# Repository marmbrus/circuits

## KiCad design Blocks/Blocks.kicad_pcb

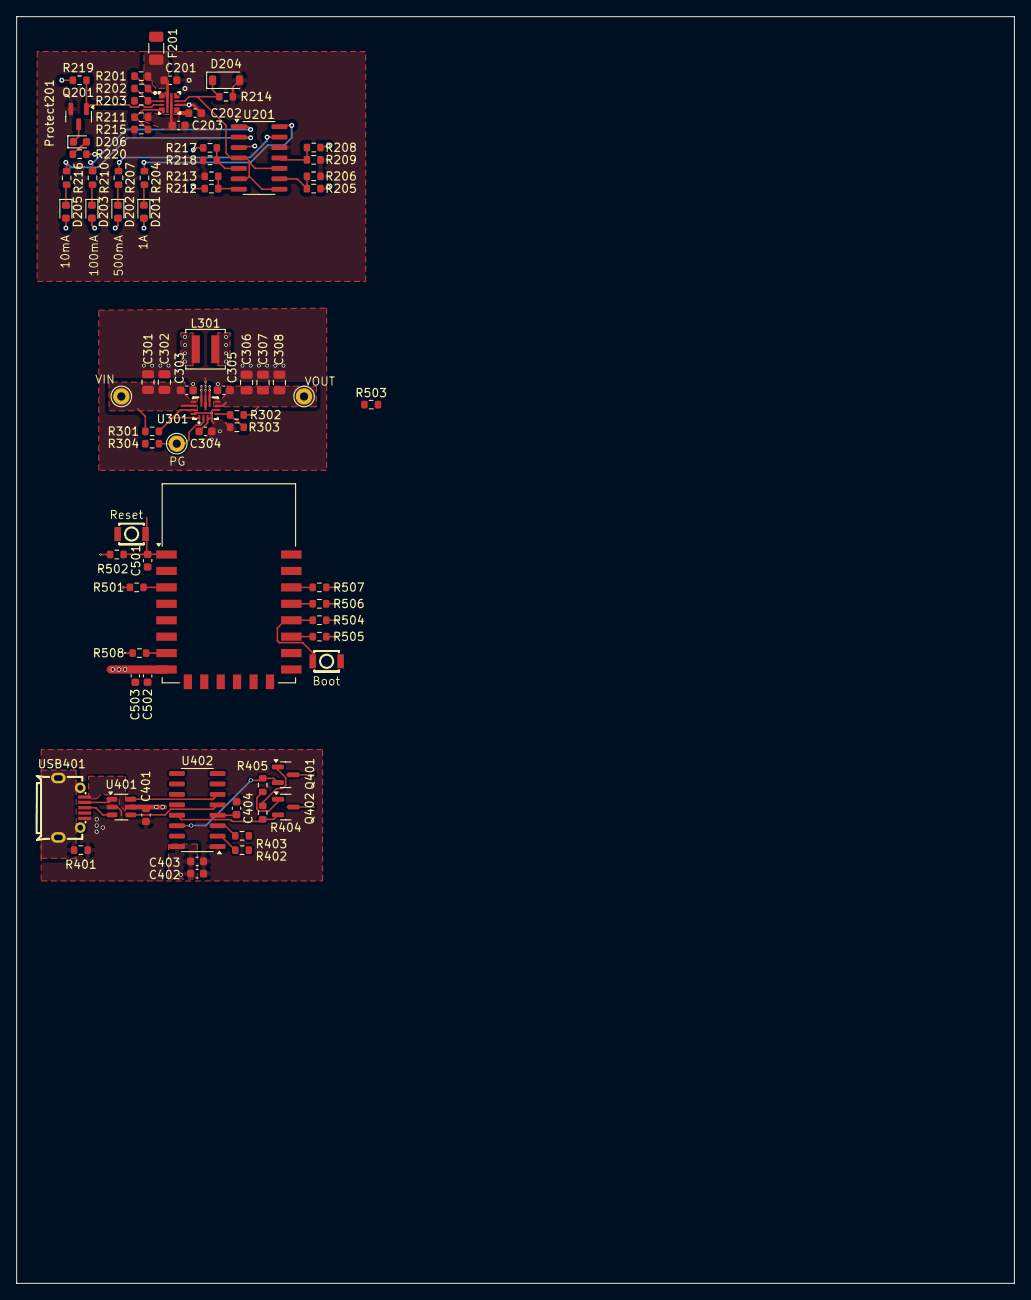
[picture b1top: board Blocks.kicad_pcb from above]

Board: 4 copper layers, 121.5 x 154.2 mm, 78 parts (0 on the bottom side), 54 nets.

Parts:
C201, C203: 1uf; C_0603_1608Metric
C202: 2.7nf; C_0603_1608Metric
C301, C302: 10uf; C_0805_2012Metric
C303, C305, C402, C502: 10uf; C_0603_1608Metric
C304, C401, C403, C404, C503: 100nf; C_0603_1608Metric
C306, C307, C308: 22uf; C_0805_2012Metric
C501: 470pf; C_0603_1608Metric
D201, D202, D203, D205, D206: LED; LED_0603_1608Metric
D204: 1.8V; D_SOD-123
F201: 2A; Fuse_1206_3216Metric
L301: 1uH; L_Coilcraft_XAL4020-XXX
Protect201: LM73100RPWR; VQFN-10_L2.0-W2.0-P0.45-TL
Q201: 2N7002; SOT-23
Q401, Q402: MMBT3904; SOT-23
R201, R211: 470k; R_0603_1608Metric
R202: 196k; R_0603_1608Metric
R203: 54.9k; R_0603_1608Metric
R204, R207, R210, R216, R220: 150; R_0603_1608Metric
R205: 5.6k; R_0603_1608Metric
R206, R209, R213, R218: 1k; R_0603_1608Metric
R208, R404, R405: 12k; R_0603_1608Metric
R212: 68k; R_0603_1608Metric
R214: 4120; R_0603_1608Metric
R215: 249k; R_0603_1608Metric
R217: 680k; R_0603_1608Metric
R219, R301, R304, R501, R502, R503, R504, R505: 10k; R_0603_1608Metric
R302: 332k; R_0603_1608Metric
R303: 51k; R_0603_1608Metric
R401: 0; R_0603_1608Metric
R402, R403: 480; R_0603_1608Metric
R506, R507, R508: 4.7k; R_0603_1608Metric
SW501, SW502: B3U-1000P; KEY-SMD_B3U-1000PM
TP301, TP302, TP303: TestPoint; Pin_D1.0mm_L10.0mm
U201: LM339; SOIC-14_3.9x8.7mm_P1.27mm
U301: TPS63070RNMR; VQFN-HR-15_L3.0-W2.5-P0.50-BL_TPS63070RNMR
U401: USBLC6-2SC6; SOT-23-6
U402: CH340C; SOIC-16_3.9x9.9mm_P1.27mm
U501: ESP-12F; ESP-12E
USB401: MICROXNJ; MICRO-USB-SMD_MICROXNJ

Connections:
+5V: D201.2 (A), D202.2 (A), D203.2 (A), D205.2 (A), R205.1, R208.1, R212.1, R217.1, R219.1, R220.2, U201.3 (V+)
/BB6V/PG: R304.2, TP302.1, U301.2 (PG)
/BB6V/VIN: C301.1, C302.1, C303.1, R301.1, TP301.1, U301.12 (Vin), U301.13 (Vin)
/BB6V/VOUT: C305.1, C306.1, C307.1, C308.1, R302.1, TP303.1, U301.7 (Vout), U301.8 (Vout)
/ESP12F/3V3: C502.1, C503.1, R501.1, R502.1, R504.1, R505.1, R506.1, R507.1, R508.1, U501.8 (VCC)
/ESP12F/BOOT: R504.2, SW502.1, U501.18 (GPIO0)
/ESP12F/ONEW: R508.2, U501.7 (GPIO13)
/ESP12F/RST: C501.2, R502.2, SW501.2, U501.1 (~RST)
/ESP12F/SCL: R507.2, U501.20 (GPIO5)
/ESP12F/SDA: R506.2, U501.19 (GPIO4)
/PP3V16V/Fused: C201.2, F201.2, Protect201.5 (IN), R201.2
/PP3V16V/IMON: D204.1 (C), Protect201.9 (IMON), R214.2, U201.4 (-), U201.6 (-), U201.8 (-), U201.10 (-)
/PP3V16V/PG: Protect201.3 (PG), Q201.1 (G), R219.2
/PP3V16V/VOUT: C203.2, Protect201.6 (OUT), R211.2
/usb_serial/VUSB: C401.1, C402.1, C403.1, U401.5 (VBUS), U402.16 (VCC), USB401.1 (VBUS)
GND: C201.1, C202.2, C203.1, C301.2, C302.2, C303.2, C304.2, C305.2, C306.2, C307.2, C308.2, C401.2, C402.2, C403.2, C404.1, C501.1, C502.2, C503.2, D204.2 (A), Protect201.8 (GND), Q201.2 (S), R203.1, R206.2, R209.2, R213.2, R214.1, R215.1, R218.2, R303.2, R401.2, R503.2, SW501.1, SW502.2, U201.12 (V-), U301.4 (GND), U301.6 (FB2), U301.10 (PGND), U301.15 (Vsel), U401.2 (GND), U402.1 (GND), U501.15 (GND), USB401.5 (GND)
unnamed: D201.1 (K), R204.2
unnamed: D202.1 (K), R207.2
unnamed: D203.1 (K), R210.2
unnamed: D205.1 (K), R216.2
unnamed: D206.2 (A), R220.1
unnamed: D206.1 (K), Q201.3 (D)
unnamed: C202.1, Protect201.7 (DVDT)
unnamed: Protect201.1 (EN/UVLO), R201.1, R202.2
unnamed: Protect201.2 (OVLO), R202.1, R203.2
unnamed: Protect201.4 (PGTH), R211.1, R215.2
unnamed: Q401.1 (B), R404.1
unnamed: Q401.2 (E), R405.2, U402.14 (~RTS)
unnamed: Q402.1 (B), R405.1
unnamed: Q402.2 (E), R404.2, U402.13 (~DTR)
unnamed: R204.1, U201.14
unnamed: R207.1, U201.13
unnamed: R210.1, U201.1
unnamed: R216.1, U201.2
unnamed: R217.2, R218.1, U201.5 (+)
unnamed: R212.2, R213.1, U201.7 (+)
unnamed: R208.2, R209.1, U201.11 (+)
unnamed: R205.2, R206.1, U201.9 (+)
unnamed: R301.2, U301.1 (PS/SYNC), U301.14 (EN)
unnamed: R302.2, R303.1, U301.5 (FB)
unnamed: L301.1, U301.11 (L1)
unnamed: L301.2, U301.9 (L2)
unnamed: C304.1, U301.3 (Vaux)
unnamed: R403.2, U402.3 (RXD)
unnamed: R402.1, U402.2 (TXD)
unnamed: U401.4 (I/O2), U402.5 (UD+)
unnamed: U401.6 (I/O1), U402.6 (UD-)
unnamed: C404.2, U402.4 (V3)
unnamed: R501.2, U501.3 (EN)
unnamed: R505.2, U501.17 (GPIO2)
unnamed: R503.1, U501.16 (GPIO15)
unnamed: U401.3 (I/O2), USB401.3 (D+)
unnamed: U401.1 (I/O1), USB401.2 (D-)
unnamed: R401.1, USB401.6 (SH1), USB401.7 (SH2), USB401.8 (SH3), USB401.9 (SH4)

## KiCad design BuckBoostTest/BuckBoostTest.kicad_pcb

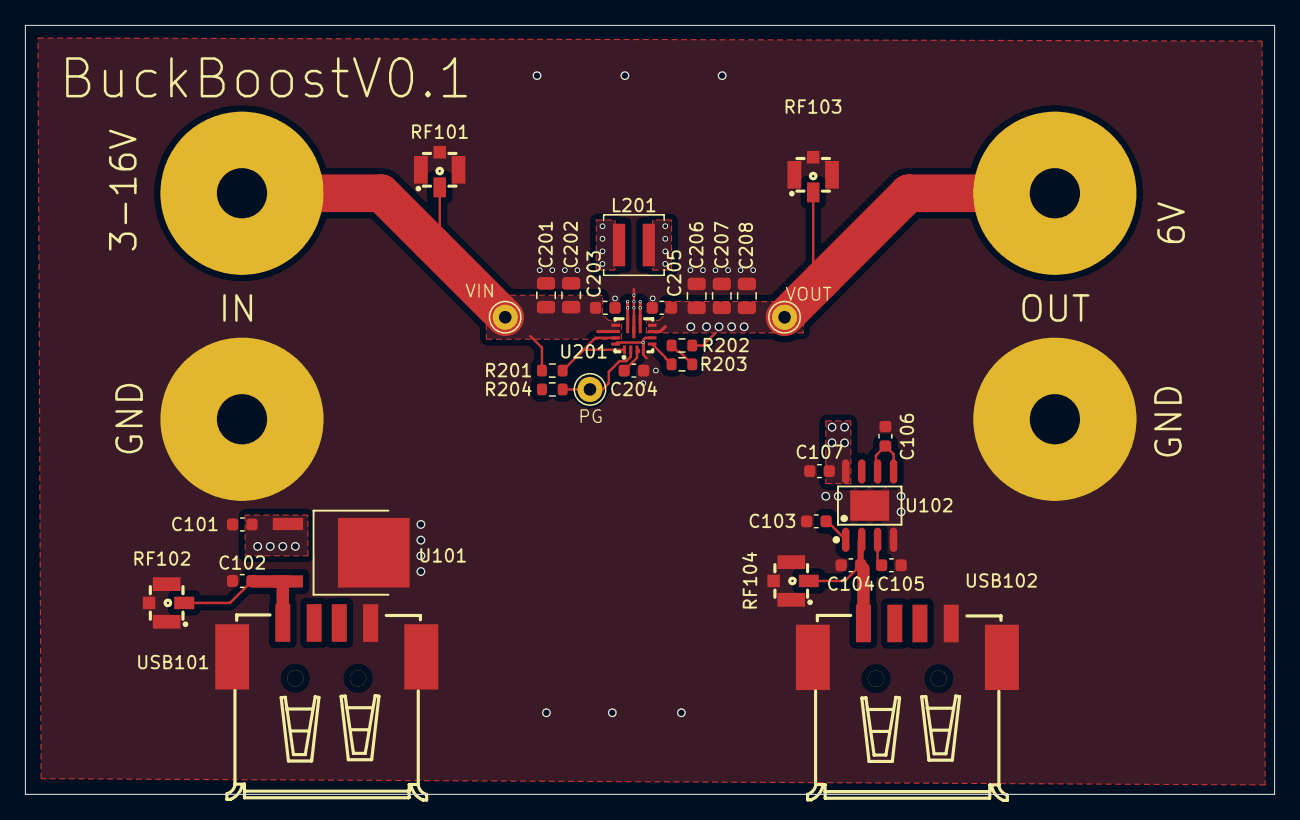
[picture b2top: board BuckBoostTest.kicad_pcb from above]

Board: 4 copper layers, 99.5 x 61.2 mm, 36 parts (0 on the bottom side), 15 nets.

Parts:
BP101, BP102, BP103, BP104: BananaPlug
C101, C102, C103, C104, C107, C203, C205: 10uf; C_0603_1608Metric
C105, C106: 1uf; C_0603_1608Metric
C201, C202: 10uf; C_0805_2012Metric
C204: 100nf; C_0603_1608Metric
C206, C207, C208: 22uf; C_0805_2012Metric
L201: 1uH; L_Coilcraft_XAL4020-XXX
R201, R204: 10k; R_0603_1608Metric
R202: 332k; R_0603_1608Metric
R203: 51k; R_0603_1608Metric
RF101, RF102, RF103, RF104: 73412-0110; ANT-SMD_73412-0110
TP201, TP202, TP203: TestPoint; Pin_D1.0mm_L10.0mm
U101: MC7805CDTRKG; TO-252-2_L6.6-W6.1-P4.58-LS9.9-TL
U102: ADM7150ARDZ-5.0; SOIC-8_L4.9-W3.9-P1.27-LS6.0-BL-EP
U201: TPS63070RNMR; VQFN-HR-15_L3.0-W2.5-P0.50-BL_TPS63070RNMR
USB101, USB102: AF180QT1.0; USB-A-SMD_AF180QT1.0

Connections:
/BB6V/PG: R204.2, TP202.1, U201.2 (PG)
/BB6V/VIN: BP101.1 (IN), C201.1, C202.1, C203.1, R201.1, RF101.2 (SIG), TP201.1, U201.12 (Vin), U201.13 (Vin)
/BB6V/VOUT: BP103.1 (IN), C101.2, C107.1, C205.1, C206.1, C207.1, C208.1, R202.1, RF103.2 (SIG), TP203.1, U101.1 (Input), U102.7 (EN), U102.8 (VIN), U201.7 (Vout), U201.8 (Vout)
GND: BP102.1 (IN), BP104.1 (IN), C101.1, C102.1, C103.2, C104.2, C105.2, C106.2, C107.2, C201.2, C202.2, C203.2, C204.2, C205.2, C206.2, C207.2, C208.2, RF101.1 (GND), RF101.3 (GND), RF101.4 (GND), RF102.1 (GND), RF102.3 (GND), RF102.4 (GND), RF103.1 (GND), RF103.3 (GND), RF103.4 (GND), RF104.1 (GND), RF104.3 (GND), RF104.4 (GND), U101.2 (Ground), U102.4 (GND), U102.9 (EP), U201.4 (GND), U201.6 (FB2), U201.10 (PGND), U201.15 (Vsel), USB101.4 (GND), USB101.5 (SH1), USB101.6 (SH2), USB102.4 (GND), USB102.5 (SH1), USB102.6 (SH2)
unnamed: R202.2, R203.1
unnamed: C102.2, RF102.2 (SIG), U101.3 (Output), USB101.1 (VCC)
unnamed: C104.1, RF104.2 (SIG), U102.2 (VOUT), USB102.1 (VCC)
unnamed: C105.1, U102.3 (BYP)
unnamed: C106.1, U102.5 (REF_SENSE), U102.6 (REF)
unnamed: C103.1, U102.1 (VREG)
unnamed: R201.2, U201.1 (PS/SYNC), U201.14 (EN)
unnamed: R203.2, U201.5 (FB)
unnamed: L201.1, U201.11 (L1)
unnamed: L201.2, U201.9 (L2)
unnamed: C204.1, U201.3 (Vaux)

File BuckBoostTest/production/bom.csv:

Designator,Footprint,Quantity,Value,LCSC Part #
"C101, C103, C104, C106, C107, C203, C205",0603,7,10uf,
"C102, C105",0603,2,1uf,
"C201, C202",0805,2,10uf,
C204,0603,1,100nf,
"C206, C207, C208",0805,3,22uf,
L201,L_Coilcraft_XAL4020-XXX,1,1uH,C4555951
"R201, R204",0603,2,10k,
R202,0603,1,332k,
R203,0603,1,51k,
"RF101, RF102, RF103, RF104",ANT-SMD_73412-0110,4,73412-0110,C434806
U101,TO-252-2_L6.6-W6.1-P4.58-LS9.9-TL,1,MC7805CDTRKG,C54285
U102,SOIC-8_L4.9-W3.9-P1.27-LS6.0-BL-EP,1,ADM7150ARDZ-5.0,C208034
U201,VQFN-HR-15_L3.0-W2.5-P0.50-BL_TPS63070RNMR,1,TPS63070RNMR,C109322
"USB101, USB102",USB-A-SMD_AF180QT1.0,2,AF180QT1.0,C404963

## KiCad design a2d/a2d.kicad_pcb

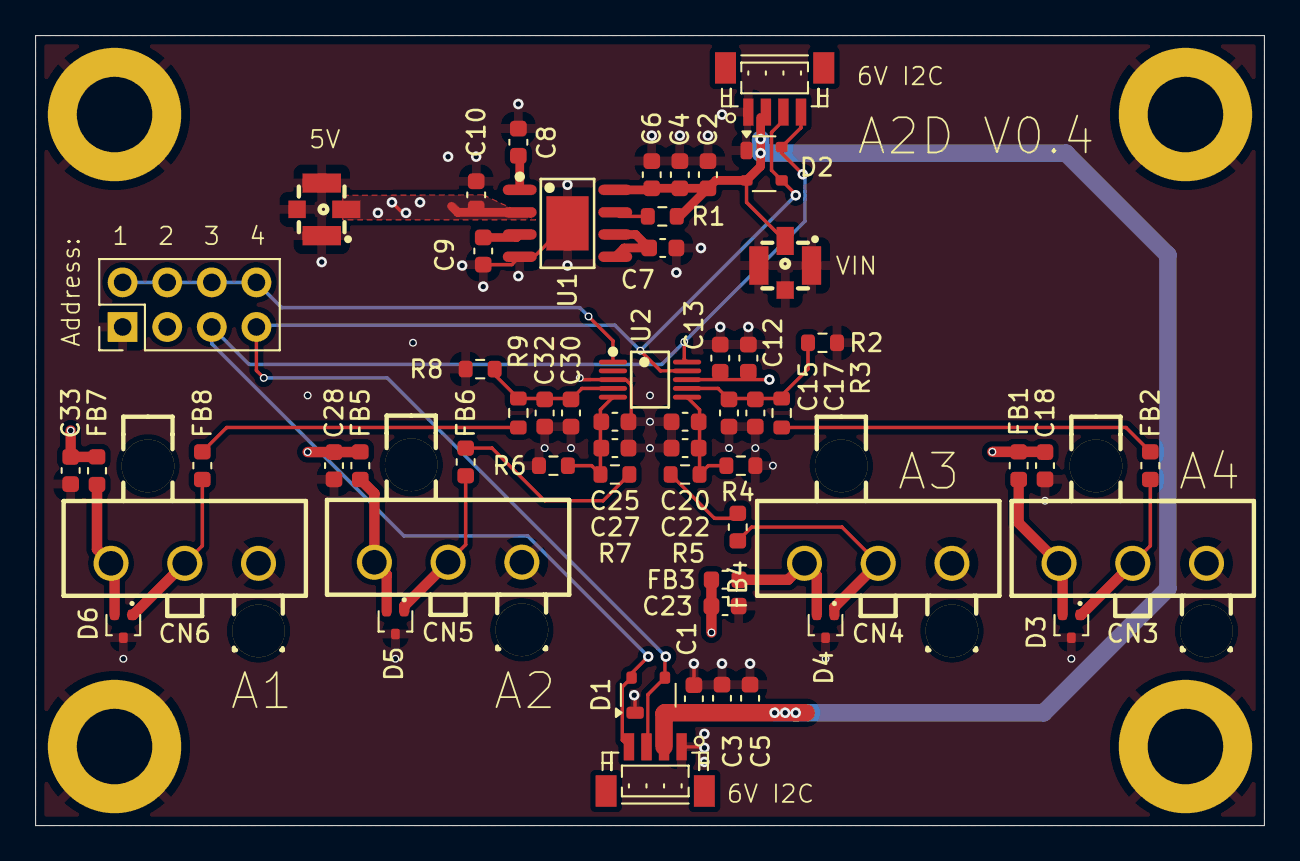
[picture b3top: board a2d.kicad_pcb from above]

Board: 4 copper layers, 70.0 x 45.0 mm, 62 parts (0 on the bottom side), 26 nets.

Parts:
C1, C2, C13: 100nf; C_0603_1608Metric
C3, C4, C7, C9, C12: 1uf; C_0603_1608Metric
C5, C6, C8, C10: 10uf; C_0603_1608Metric
C15, C18, C20, C23, C25, C28, C30, C33: 100nF; C_0603_1608Metric
C17, C22, C27, C32: 3.3uF; C_0603_1608Metric
CN1, CN2: BM04B-SRSS-TB(LF)(SN); CONN-SMD_BM04B-SRSS-TB
CN3, CN4, CN5, CN6: 39302030; CONN-TH_3P-P4.20_39302030
D1, D2: SP0503BAHT; SOT-143
D3, D4, D5, D6: RCLAMP0502B; SOT-416
FB1, FB2, FB3, FB4, FB5, FB6, FB7, FB8: FerriteBead; L_0603_1608Metric
H1, H2, H3, H4: MountingHole_Pad; MountingHole_4.3mm_M4_ISO7380_Pad
J1: Conn_02x04_Odd_Even; PinHeader_2x04_P2.54mm_Vertical
R1, R3, R5, R7, R9: 10k; R_0603_1608Metric
R2, R4, R6, R8: 5.1M; R_0603_1608Metric
RF1, RF2: 73412-0110; ANT-SMD_73412-0110
U1: ADM7150ARDZ-5.0; SOIC-8_L4.9-W3.9-P1.27-LS6.0-BL-EP
U2: ADS1115IDGSR; MSOP-10_L3.0-W3.0-P0.50-LS5.0-BL

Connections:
+5V: C10.1, C12.1, C13.1, C18.1, C23.1, C28.1, C33.1, FB1.2, FB3.2, FB5.2, FB7.2, J1.3, RF2.2 (SIG), U1.2 (VOUT), U2.8 (VDD)
/6V: C1.1, C2.1, C3.1, C4.1, C5.1, C6.1, CN1.2, CN2.2, D1.2 (K), D2.2 (K), R1.1, RF1.2 (SIG), U1.8 (VIN)
/A1: C30.2, C32.2, R8.2, R9.1, U2.4 (AIN0)
/A2: C25.2, C27.2, R6.2, R7.1, U2.5 (AIN1)
/A3: C20.2, C22.2, R4.2, R5.1, U2.6 (AIN2)
/A4: C15.2, C17.2, R2.2, R3.1, U2.7 (AIN3)
/SCL: CN1.4, CN2.4, D1.4 (K), D2.4 (K), J1.5, U2.10 (SCL)
/SDA: CN1.3, CN2.3, D1.3 (K), D2.3 (K), J1.7, U2.9 (SDA)
GND: C1.2, C2.2, C3.2, C4.2, C5.2, C6.2, C7.1, C8.2, C9.1, C10.2, C12.2, C13.2, C15.1, C17.1, C18.2, C20.1, C22.1, C23.2, C25.1, C27.1, C28.2, C30.1, C32.1, C33.2, CN1.1, CN2.1, CN3.3, CN4.3, CN5.3, CN6.3, D1.1 (A), D2.1 (A), D3.3 (A), D4.3 (A), D5.3 (A), D6.3 (A), H1.1, H2.1, H3.1, H4.1, J1.1, R2.1, R4.1, R6.1, R8.1, RF1.1 (GND), RF1.3 (GND), RF1.4 (GND), RF2.1 (GND), RF2.3 (GND), RF2.4 (GND), U1.4 (GND), U1.9 (EP), U2.3 (GND)
unnamed: CN3.2, D3.1 (K1), FB2.1
unnamed: CN3.1, D3.2 (K2), FB1.1
unnamed: CN4.2, D4.1 (K1), FB4.1
unnamed: CN4.1, D4.2 (K2), FB3.1
unnamed: CN5.2, D5.1 (K1), FB6.1
unnamed: CN5.1, D5.2 (K2), FB5.1
unnamed: CN6.2, D6.1 (K1), FB8.1
unnamed: CN6.1, D6.2 (K2), FB7.1
unnamed: FB2.2, R3.2
unnamed: FB4.2, R5.2
unnamed: FB6.2, R7.2
unnamed: FB8.2, R9.2
unnamed: J1.2, J1.4, J1.6, J1.8, U2.1 (ADDR)
unnamed: C9.2, U1.3 (BYP)
unnamed: R1.2, U1.7 (EN)
unnamed: C7.2, U1.5 (REF_SENSE), U1.6 (REF)
unnamed: C8.1, U1.1 (VREG)

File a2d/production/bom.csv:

Designator,Footprint,Quantity,Value,LCSC Part #
"C1, C13, C15, C18, C2, C20, C23, C25, C28, C30, C33",0603,11,100nf,
"C10, C5, C6, C8",0603,4,10uf,
"C12, C3, C4, C7, C9",0603,5,1uf,
"C17, C22, C27, C32",0603,4,3.3uF,
"CN1, CN2",CONN-SMD_BM04B-SRSS-TB,2,BM04B-SRSS-TB(LF)(SN),C160390
"CN3, CN4, CN5, CN6",CONN-TH_3P-P4.20_39302030,4,39302030,C589033
"D1, D2",SOT-143,2,SP0503BAHT,
"D3, D4, D5, D6",SOT-416,4,RCLAMP0502B,
"FB1, FB2, FB3, FB4, FB5, FB6, FB7, FB8",0603,8,FerriteBead,C85824
J1,PinHeader_2x04_P2.54mm_Vertical,1,Conn_02x04_Odd_Even,C5383105
"R1, R3, R5, R7, R9",0603,5,10k,
"R2, R4, R6, R8",0603,4,5.1M,
U1,SOIC-8_L4.9-W3.9-P1.27-LS6.0-BL-EP,1,ADM7150ARDZ-5.0,C208034
U2,MSOP-10_L3.0-W3.0-P0.50-LS5.0-BL,1,ADS1115IDGSR,C37593

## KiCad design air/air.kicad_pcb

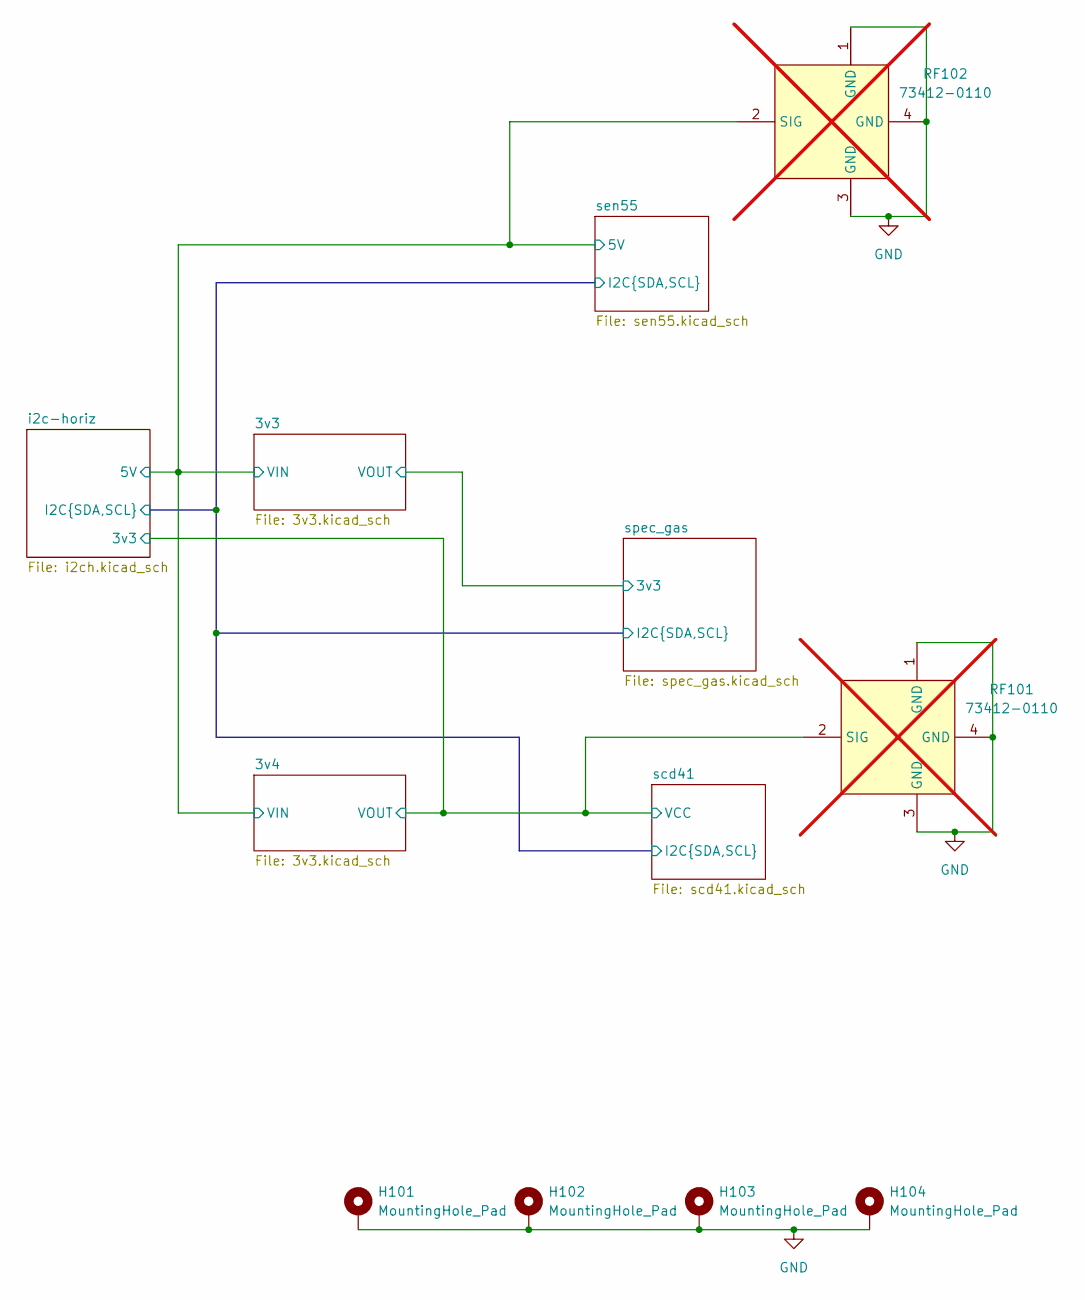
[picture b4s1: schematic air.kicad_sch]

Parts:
H101, H102, H103, H104: MountingHole_Pad; MountingHole_3.2mm_M3_Pad_Via
RF101, RF102: 73412-0110; ANT-SMD_73412-0110; LCSC Part C434806; not fitted

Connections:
/3v3/VIN: RF102.2 (SIG); also elsewhere on the board
/3v4/VOUT: RF101.2 (SIG); also elsewhere on the board
GND: H101.1, H102.1, H103.1, H104.1, RF101.1 (GND), RF101.3 (GND), RF101.4 (GND), RF102.1 (GND), RF102.3 (GND), RF102.4 (GND); also elsewhere on the board

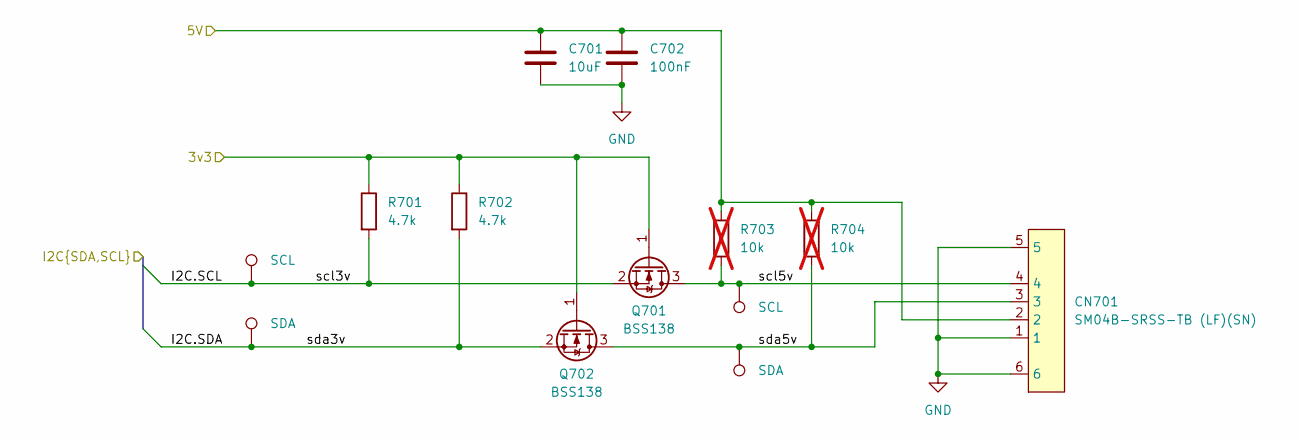
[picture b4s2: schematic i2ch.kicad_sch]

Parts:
C701: 10uF; C_0603_1608Metric
C702: 100nF; C_0603_1608Metric
CN701: SM04B-SRSS-TB (LF)(SN); CONN-SMD_4P-P1.00_SM04B-SRSS-TB-LF-SN; LCSC Part C160404
Q701, Q702: BSS138; SOT-23
R701, R702: 4.7k; R_0603_1608Metric
R703, R704: 10k; R_0603_1608Metric; not fitted
TP701, TP702, TP703, TP704: LabeledTestPoint

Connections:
/3v3/VIN: C701.1, C702.1, CN701.2, R703.1, R704.1; also elsewhere on the board
/3v4/VOUT: Q701.1 (G), Q702.1 (G), R701.1, R702.1; also elsewhere on the board
/i2c-horiz/I2C.SCL: Q701.2 (S), R701.2, TP701.1; also elsewhere on the board
/i2c-horiz/I2C.SDA: Q702.2 (S), R702.2, TP703.1; also elsewhere on the board
/i2c-horiz/scl5v: CN701.4, Q701.3 (D), R703.2, TP702.1
/i2c-horiz/sda5v: CN701.3, Q702.3 (D), R704.2, TP704.1
GND: C701.2, C702.2, CN701.1, CN701.5, CN701.6; also elsewhere on the board

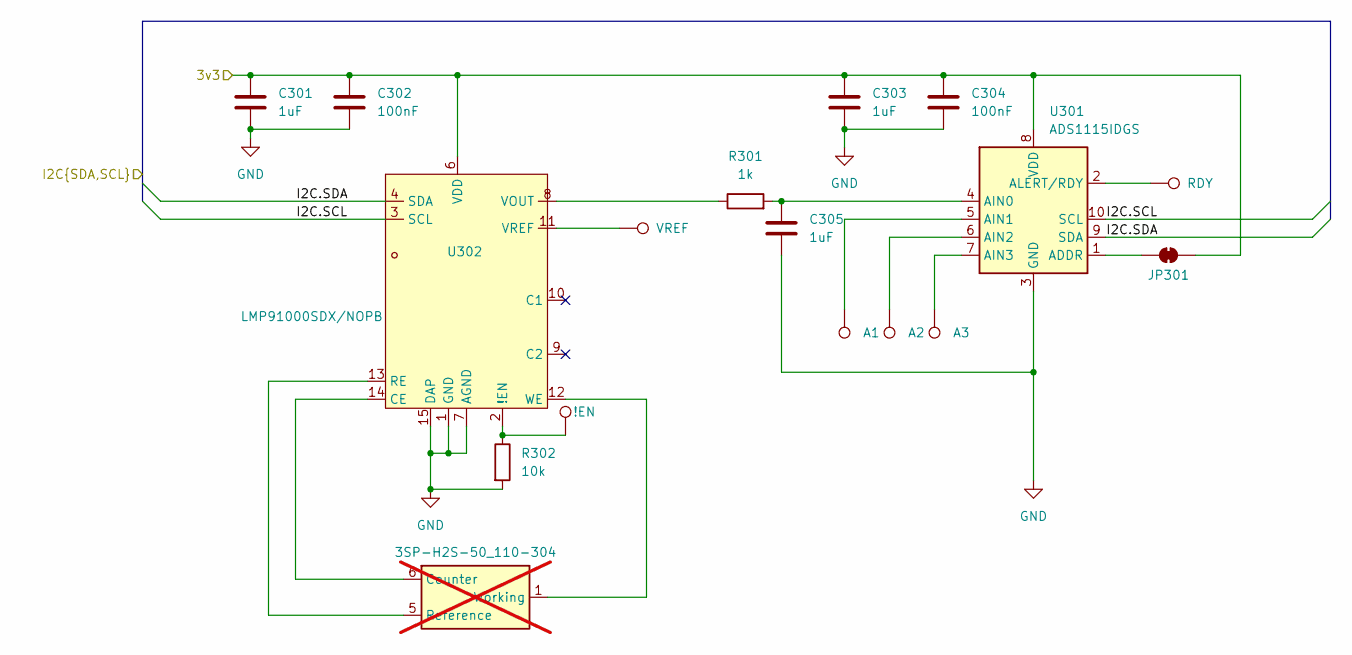
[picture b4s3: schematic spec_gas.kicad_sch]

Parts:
C301, C303, C305: 1uF; C_0603_1608Metric
C302, C304: 100nF; C_0603_1608Metric
JP301: SolderJumper_2_Bridged; SolderJumper-2_P1.3mm_Bridged2Bar_RoundedPad1.0x1.5mm
R301: 1k; R_0603_1608Metric
R302: 10k; R_0603_1608Metric
TP301, TP302, TP303, TP304, TP305, TP306: LabeledTestPoint
U301: ADS1115IDGS; TSSOP-10_3x3mm_P0.5mm
U302: LMP91000SDX/NOPB; WSON-14_L4.0-W4.0-P0.50-BL-EP-1; LCSC Part C2651584
U303: 3SP-H2S-50_110-304; SPEC_110-xxx_SMD-10Pin_20x20mm_P4.0mm; not fitted

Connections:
/3v3/VOUT: C301.1, C302.1, C303.1, C304.1, JP301.1 (A), U301.8 (VDD), U302.6 (VDD); also elsewhere on the board
/i2c-horiz/I2C.SCL: U301.10 (SCL), U302.3 (SCL); also elsewhere on the board
/i2c-horiz/I2C.SDA: U301.9 (SDA), U302.4 (SDA); also elsewhere on the board
GND: C301.2, C302.2, C303.2, C304.2, C305.2, R302.2, U301.3 (GND), U302.1 (GND), U302.7 (AGND), U302.15 (DAP); also elsewhere on the board
unnamed: JP301.2 (B), U301.1 (ADDR)
unnamed: C305.1, R301.2, U301.4 (AIN0)
unnamed: TP303.1, U301.5 (AIN1)
unnamed: TP304.1, U301.6 (AIN2)
unnamed: TP305.1, U301.7 (AIN3)
unnamed: TP301.1, U301.2 (ALERT/RDY)
unnamed: R302.1, TP306.1, U302.2 (!EN)
unnamed: U302.14 (CE), U303.6 (Counter)
unnamed: U302.13 (RE), U303.5 (Reference)
unnamed: R301.1, U302.8 (VOUT)
unnamed: TP302.1, U302.11 (VREF)
unnamed: U302.12 (WE), U303.1 (Working), U303.10 (Working)

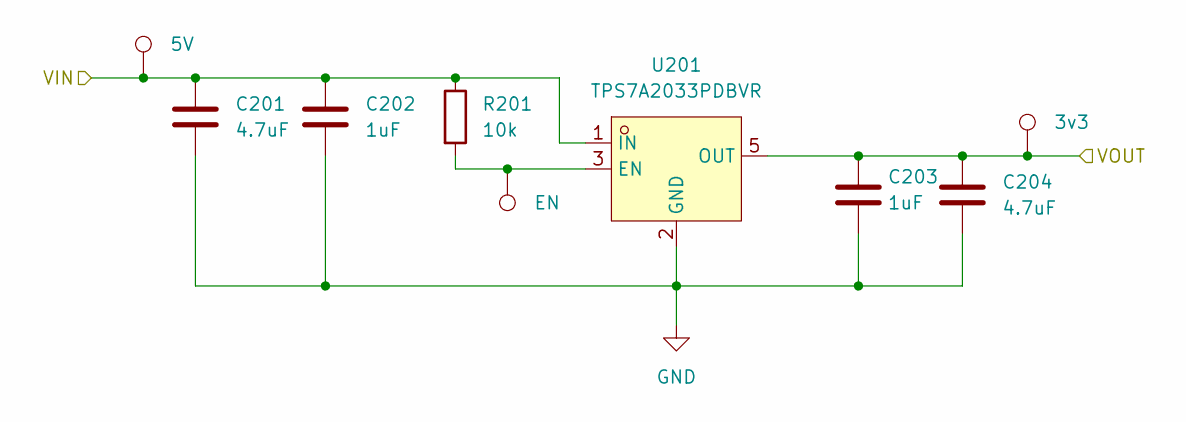
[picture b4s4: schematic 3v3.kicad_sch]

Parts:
C201, C204: 4.7uF; C_0603_1608Metric
C202, C203: 1uF; C_0603_1608Metric
R201: 10k; R_0603_1608Metric
TP201, TP202, TP203: LabeledTestPoint
U201: TPS7A2033PDBVR; SOT-23-5_L2.9-W1.6-P0.95-LS2.8-BR; LCSC Part C2862740

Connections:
/3v3/VIN: C201.1, C202.1, R201.1, TP201.1, U201.1 (IN); also elsewhere on the board
/3v4/VOUT: C203.1, C204.1, TP202.1, U201.5 (OUT); also elsewhere on the board
GND: C201.2, C202.2, C203.2, C204.2, U201.2 (GND); also elsewhere on the board
unnamed: R201.2, TP203.1, U201.3 (EN)

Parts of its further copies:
C401, C404: 4.7uF; C_0603_1608Metric
C402, C403: 1uF; C_0603_1608Metric
R401: 10k; R_0603_1608Metric
TP401, TP402, TP403: LabeledTestPoint
U401: TPS7A2033PDBVR; SOT-23-5_L2.9-W1.6-P0.95-LS2.8-BR; LCSC Part C2862740

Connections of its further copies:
/3v3/VIN: C401.1, C402.1, R401.1, TP401.1, U401.1 (IN); also elsewhere on the board
/3v3/VOUT: C403.1, C404.1, TP402.1, U401.5 (OUT); also elsewhere on the board
GND: C401.2, C402.2, C403.2, C404.2, U401.2 (GND); also elsewhere on the board
unnamed: R401.2, TP403.1, U401.3 (EN)

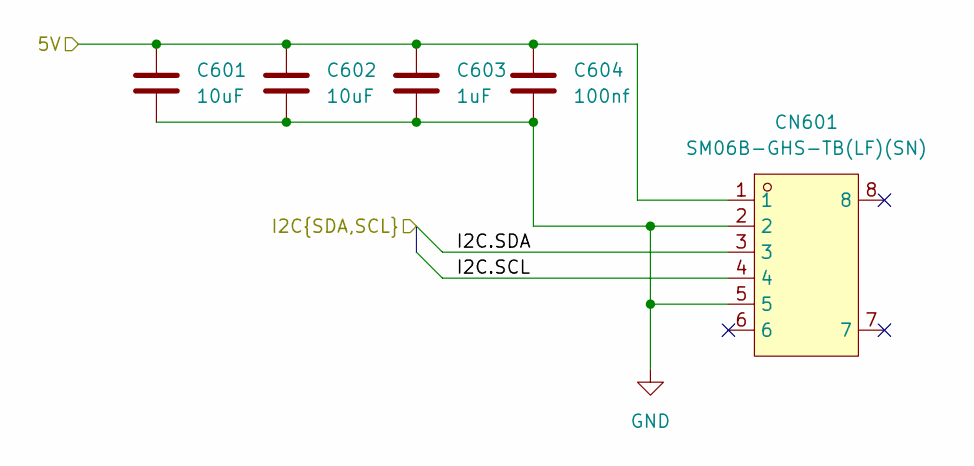
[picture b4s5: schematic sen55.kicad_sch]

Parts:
C601, C602: 10uF; C_0603_1608Metric
C603: 1uF; C_0603_1608Metric
C604: 100nf; C_0603_1608Metric
CN601: SM06B-GHS-TB(LF)(SN); CONN-TH_SM06B-GHS-TB-LF-SN; LCSC Part C133065

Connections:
/3v3/VIN: C601.1, C602.1, C603.1, C604.1, CN601.1; also elsewhere on the board
/i2c-horiz/I2C.SCL: CN601.4; also elsewhere on the board
/i2c-horiz/I2C.SDA: CN601.3; also elsewhere on the board
GND: C601.2, C602.2, C603.2, C604.2, CN601.2, CN601.5; also elsewhere on the board

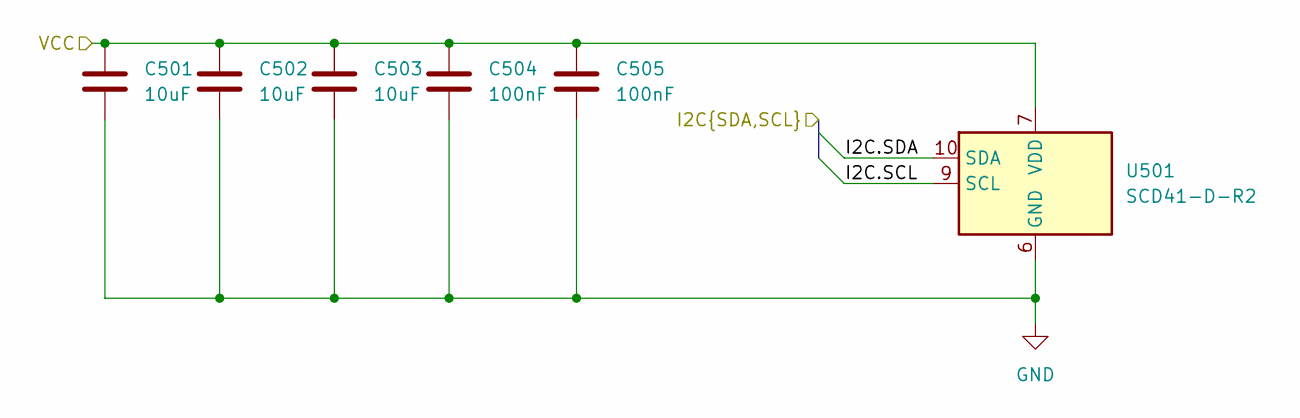
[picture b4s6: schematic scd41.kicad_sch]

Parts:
C501, C502, C503: 10uF; C_0603_1608Metric
C504, C505: 100nF; C_0603_1608Metric
U501: SCD41-D-R2; Sensirion_SCD4x-1EP_10.1x10.1mm_P1.25mm_EP4.8x4.8mm

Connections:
/3v4/VOUT: C501.1, C502.1, C503.1, C504.1, C505.1, U501.7 (VDD), U501.19 (VDD); also elsewhere on the board
/i2c-horiz/I2C.SCL: U501.9 (SCL); also elsewhere on the board
/i2c-horiz/I2C.SDA: U501.10 (SDA); also elsewhere on the board
GND: C501.2, C502.2, C503.2, C504.2, C505.2, U501.6 (GND), U501.20 (GND), U501.21 (GND); also elsewhere on the board

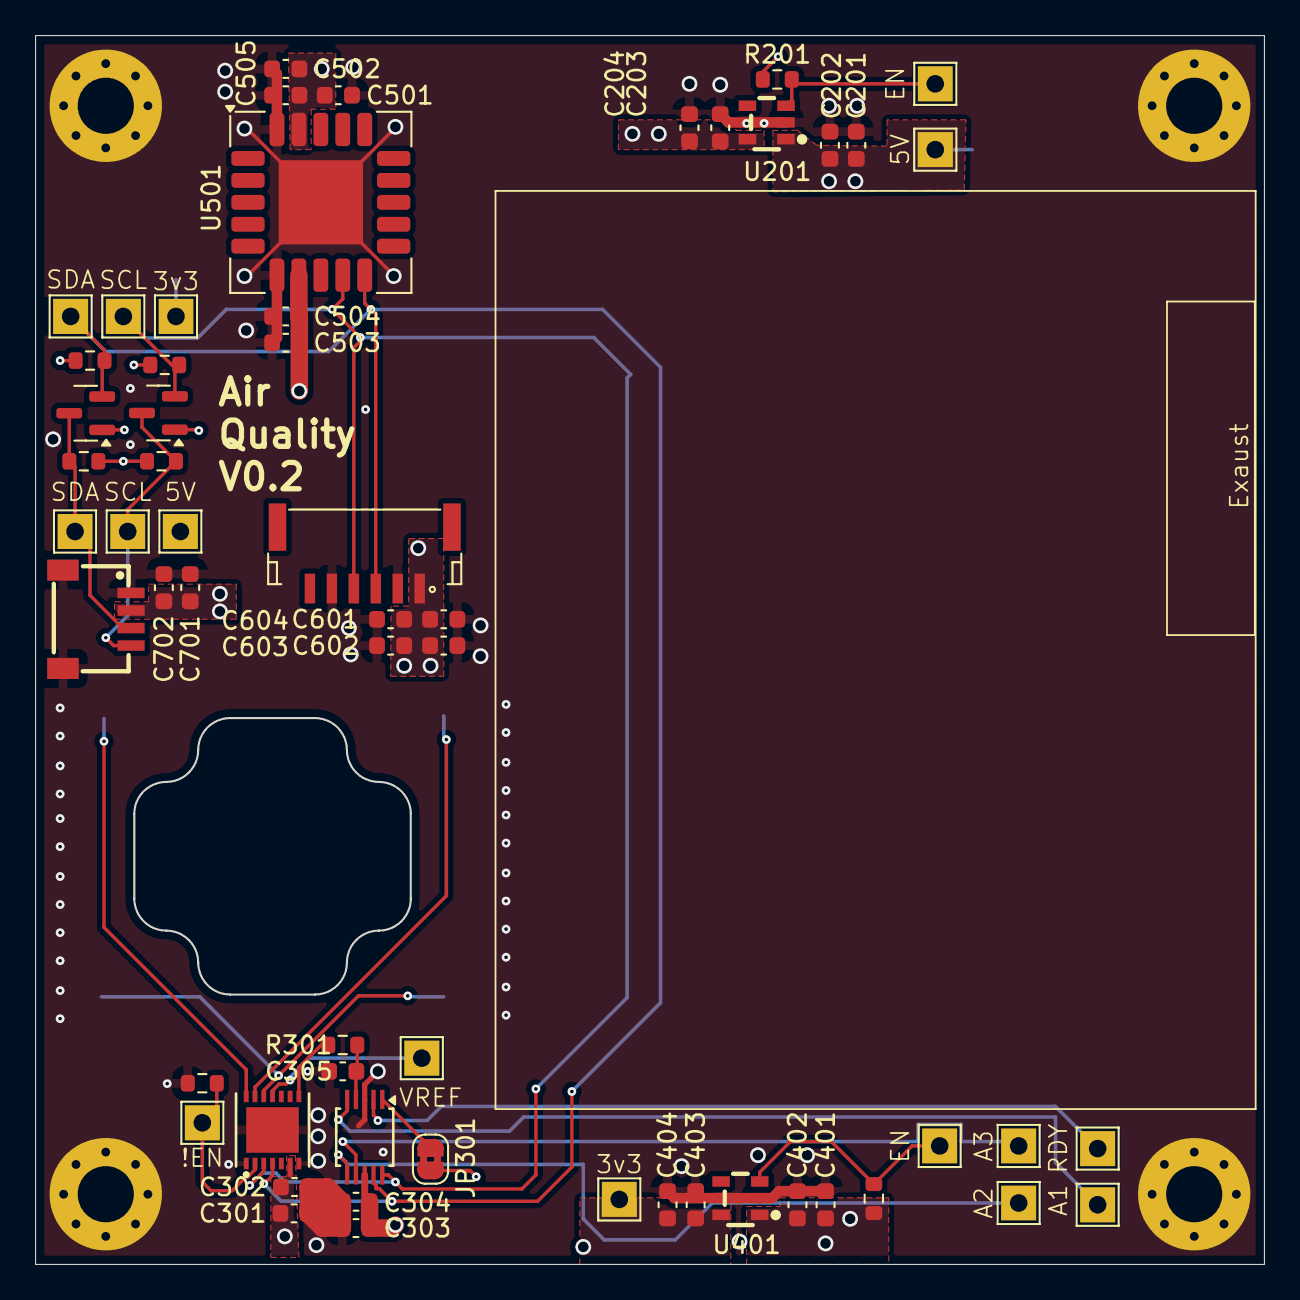
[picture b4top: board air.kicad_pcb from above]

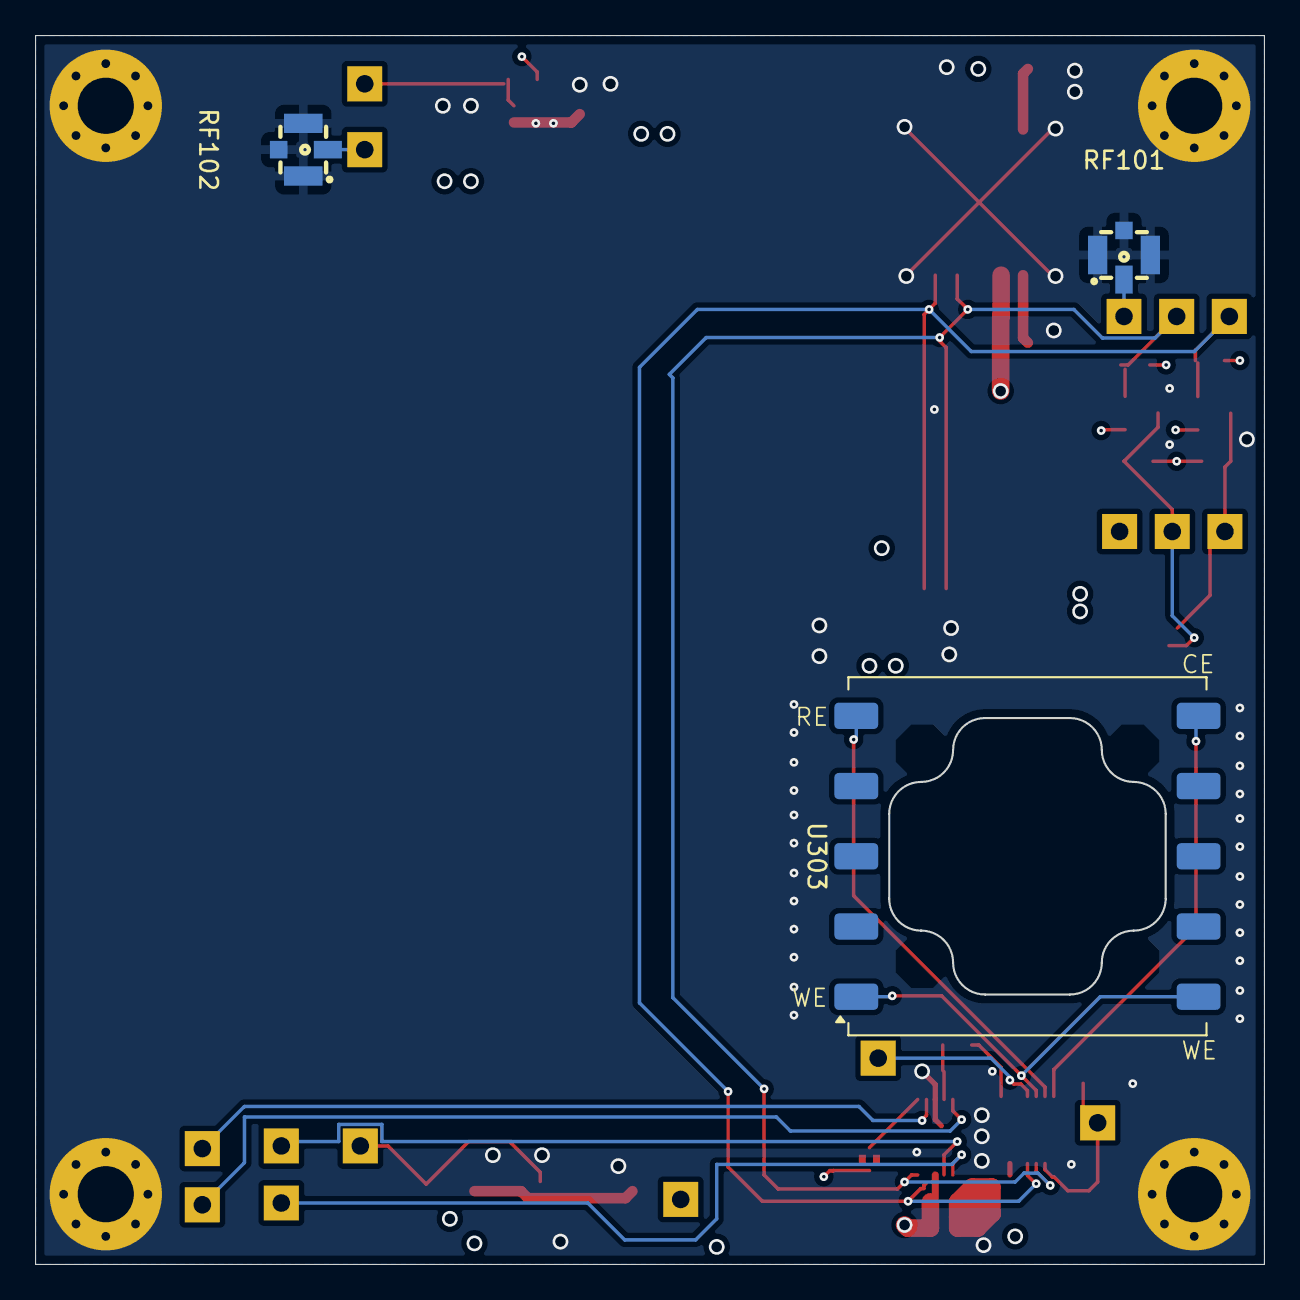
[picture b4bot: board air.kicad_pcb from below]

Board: 4 copper layers, 70.0 x 70.0 mm, 65 parts (3 on the bottom side), 22 nets.

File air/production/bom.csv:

Designator,Footprint,Quantity,Value,LCSC Part #
"C201, C204, C401, C404",0603,4,4.7uF,
"C202, C203, C301, C303, C305, C402, C403, C603",0603,8,1uF,
"C302, C304, C504, C505, C604, C702",0603,6,100nF,
"C501, C502, C503, C601, C602, C701",0603,6,10uF,
CN601,CONN-TH_SM06B-GHS-TB-LF-SN,1,SM06B-GHS-TB(LF)(SN),C133065
CN701,CONN-SMD_4P-P1.00_SM04B-SRSS-TB-LF-SN,1,SM04B-SRSS-TB (LF)(SN),C160404
"Q701, Q702",SOT-23,2,BSS138,
"R201, R302, R401",0603,3,10k,
R301,0603,1,1k,
"R701, R702",0603,2,4.7k,
"U201, U401",SOT-23-5_L2.9-W1.6-P0.95-LS2.8-BR,2,TPS7A2033PDBVR,C2862740
U301,TSSOP-10_3x3mm_P0.5mm,1,ADS1115IDGS,
U302,WSON-14_L4.0-W4.0-P0.50-BL-EP-1,1,LMP91000SDX/NOPB,C2651584
U501,Sensirion_SCD4x-1EP_10.1x10.1mm_P1.25mm_EP4.8x4.8mm,1,SCD41-D-R2,

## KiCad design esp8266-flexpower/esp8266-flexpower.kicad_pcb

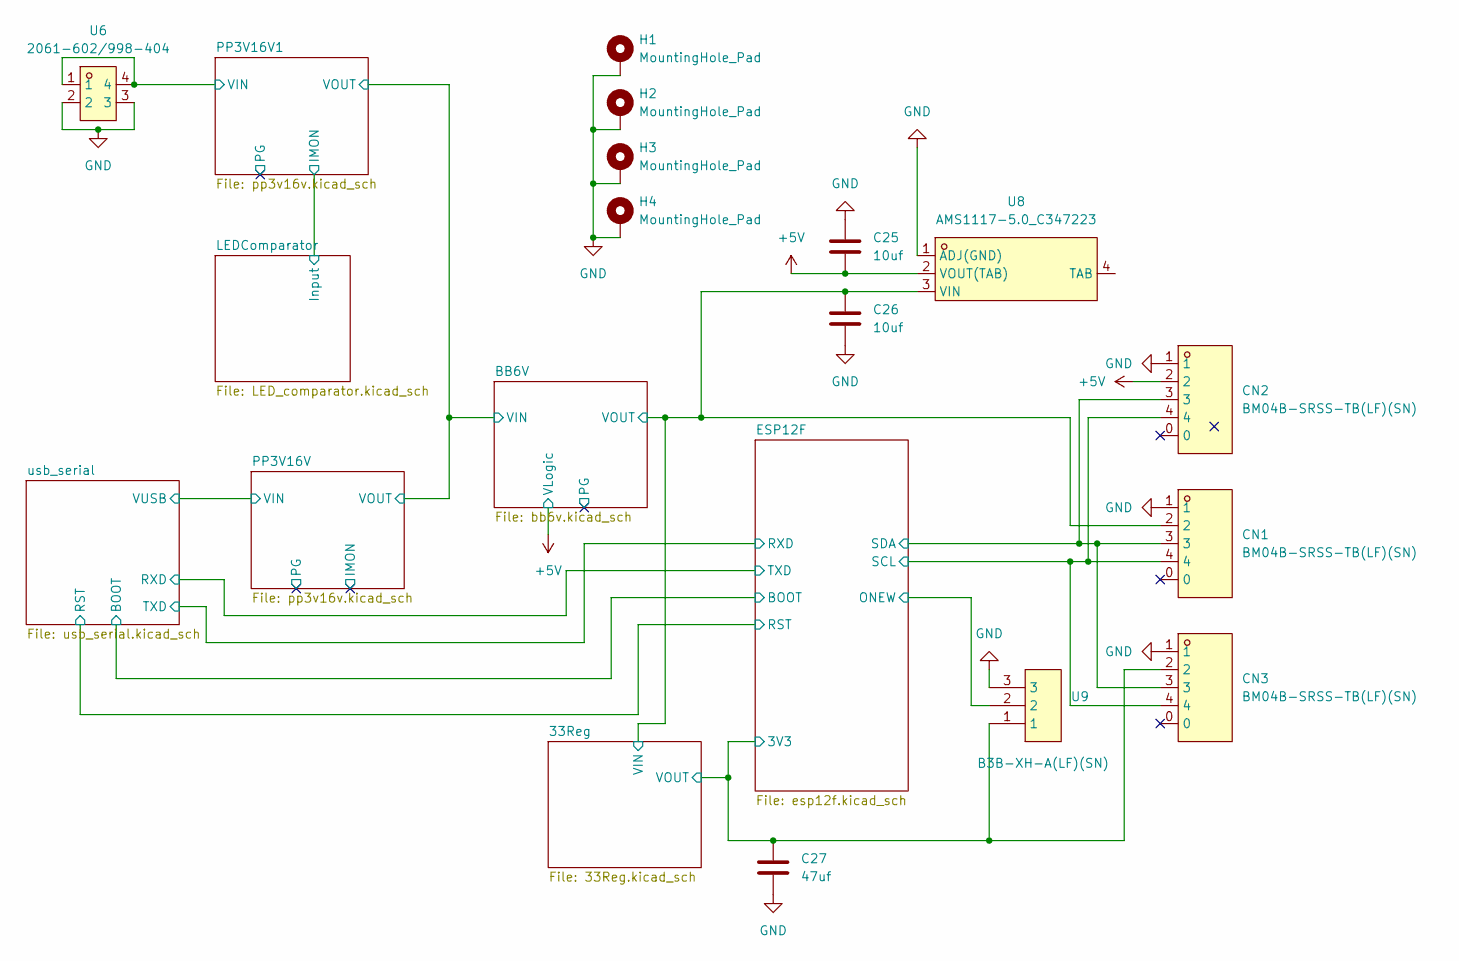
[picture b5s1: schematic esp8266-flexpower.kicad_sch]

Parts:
C25, C26: 10uf; C_0603_1608Metric
C27: 47uf; C_0603_1608Metric
CN1, CN2, CN3: BM04B-SRSS-TB(LF)(SN); CONN-SMD_BM04B-SRSS-TB; LCSC Part C160390
H1, H2, H3, H4: MountingHole_Pad; MountingHole_4.3mm_M4_ISO7380_Pad
U6: 2061-602/998-404; CONN-SMD_2061-602-998-404; LCSC Part C2765058
U8: AMS1117-5.0_C347223; SOT-223_L6.7-W3.5-P2.30-BR; LCSC Part C347223
U9: B3B-XH-A(LF)(SN); CONN-TH_3P-P2.50_A2501WV2-3P; LCSC Part C144394

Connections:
+5V: C25.2, CN2.2, U8.2 (VOUT(TAB)); also elsewhere on the board
/33Reg/VIN: C26.1, CN1.2, U8.3 (VIN); also elsewhere on the board
/33Reg/VOUT: C27.1, CN3.2, U9.1; also elsewhere on the board
/ESP12F/ONEW: U9.2; also elsewhere on the board
/ESP12F/SCL: CN1.4, CN2.4, CN3.4; also elsewhere on the board
/ESP12F/SDA: CN1.3, CN2.3, CN3.3; also elsewhere on the board
/PP3V16V1/VIN: U6.1, U6.4; also elsewhere on the board
GND: C25.1, C26.2, C27.2, CN1.1, CN2.1, CN3.1, H1.1, H2.1, H3.1, H4.1, U6.2, U6.3, U8.1 (ADJ(GND)), U9.3; also elsewhere on the board
